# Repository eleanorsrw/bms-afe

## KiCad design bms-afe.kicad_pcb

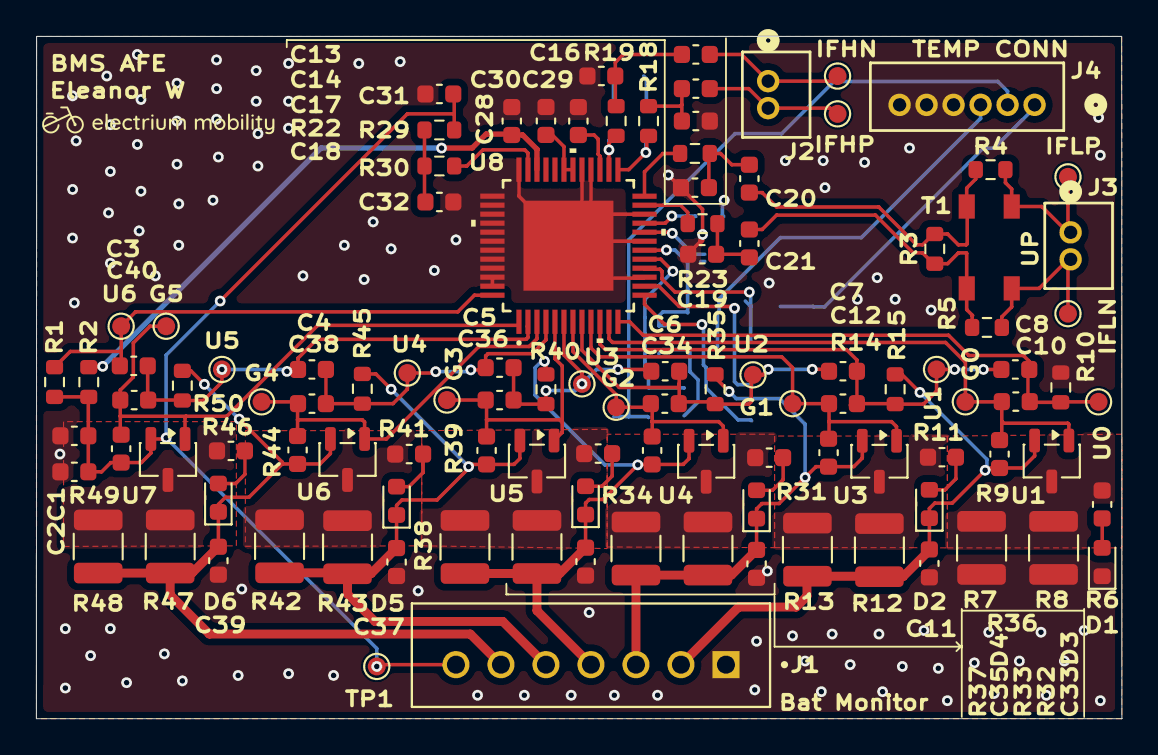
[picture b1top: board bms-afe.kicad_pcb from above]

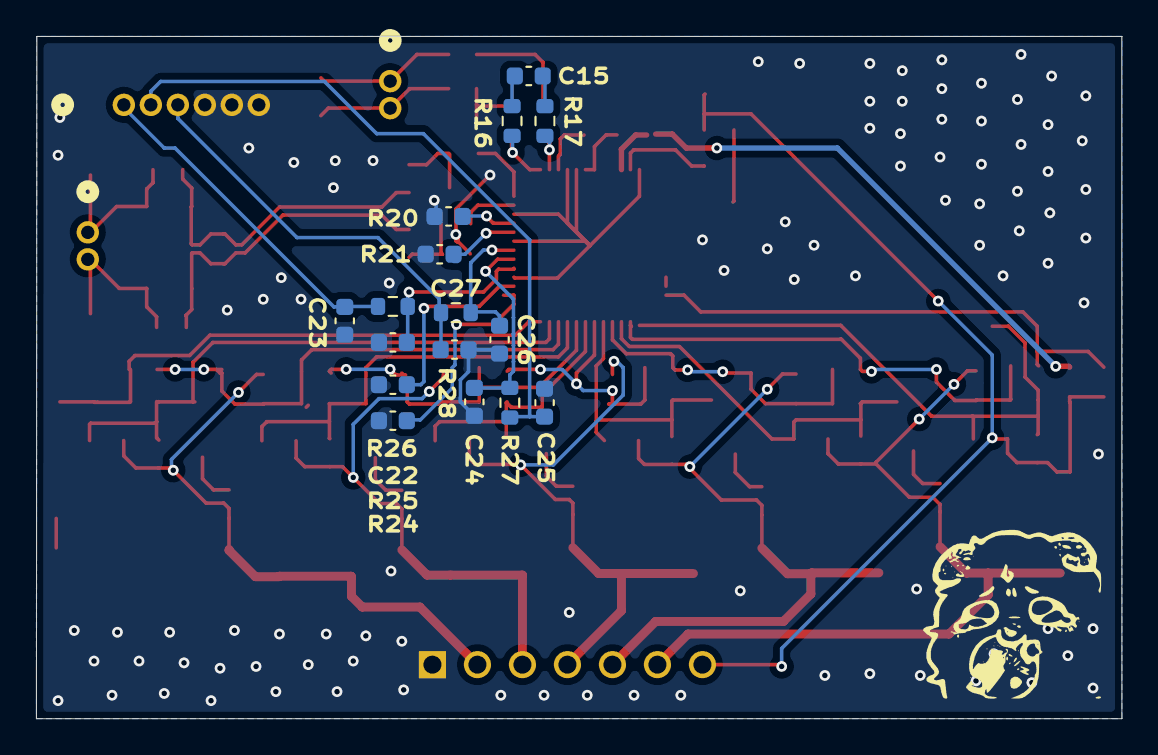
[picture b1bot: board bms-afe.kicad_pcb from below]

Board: 2 copper layers, 60.3 x 37.9 mm, 125 parts (16 on the bottom side), 63 nets.

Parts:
C1, C2, C11, C33, C35, C37, C39: CAP CER 1000PF 50V X7R 0603; C_0603_1608Metric
C3, C4, C5, C6, C7, C8: CAP CER 0.33UF 16V X7R 0603; C_0603_1608Metric
C10, C12, C34, C36, C38, C40: CAP CER 0.1UF 25V X7R 0603; C_0603_1608Metric
C13, C14, C20, C21: CAP CER 0603 1NF 16V X7R 10%; C_0603_1608Metric
C15: CAP CER 250PF 25V NP0 0603; C_0603_1608Metric
C16, C17, C18, C19: CAP CER 220PF 50V X7R 0603; C_0603_1608Metric
C22, C24, C26: 10nF; C_0603_1608Metric
C23, C25, C27: 4.7nF; C_0603_1608Metric
C28: 0.1uF; C_0603_1608Metric
C29: 0.33uF; C_0603_1608Metric
C30, C32: 100nF; C_0603_1608Metric
C31: 1nF; C_0603_1608Metric
D1, D2, D3, D4, D5, D6: 1.6X0.8MM RED/WHT SMD LED; D_0603_1608Metric
G0, G1, G2, G3, G4, G5: TestPoint; TestPoint_Pad_D1.0mm
IFHN: TestPoint; TestPoint_Pad_D1.0mm
IFHP: TestPoint; TestPoint_Pad_D1.0mm
IFLN: TestPoint; TestPoint_Pad_D1.0mm
IFLP: TestPoint; TestPoint_Pad_D1.0mm
J1: CONN HEADER VERT 7POS 2.5MM; JST_B7B-XH-A_LF__SN_
J2, J3: CONN HEADER VERT 2POS 1.5MM; CONN_B2B-ZR_02P_JST
J4: CONN HEADER VERT 6POS 1.5MM; CONN_B6B-ZR_JST
R1, R10, R15, R35, R40, R45, R50: RES 10 OHM 1% 1/10W 0603; R_0603_1608Metric
R2: RES SMD 5.1 OHM 1% 1/8W 0603; R_0603_1608Metric
R3: RES SMD 1K OHM 0.1% 1/10W 0603; R_0603_1608Metric
R4, R5: 0; R_0603_1608Metric
R6, R11, R31, R36, R41, R46: RES SMD 487 OHM 1% 1/10W 0603; C_0603_1608Metric
R7, R8, R12, R13, R32, R33, R37, R38, R42, R43, R47, R48: RES SMD 52.3 OHM 1% 1/2W 1210; C_1210_3225Metric
R9, R14, R34, R39, R44, R49: RES SMD 8.2 OHM 1% 1/8W 0603; C_0603_1608Metric
R16, R26: RES 100 OHM 1% 1/10W 0603; R_0603_1608Metric
R17: 100; R_0603_1608Metric
R18, R19, R22, R23: RES SMD 39 OHM 5% 1/8W 0603; R_0603_1608Metric
R20, R21, R24, R25: 20k; C_0603_1608Metric
R27, R28: RES SMD 10K OHM 1% 1/8W 0603; R_0603_1608Metric
R29: 10; R_0603_1608Metric
R30: 5.1; R_0603_1608Metric
T1: PULSE XFMR 15UH 1 OHM FOR PLC; AMT45S-150-2P-TL000
TP1: TestPoint; TestPoint_Pad_D1.0mm
U0, U1, U2, U3#2, U4#2, U5#2, U6#2: TestPoint; TestPoint_Pad_D1.0mm
U1#2, U3, U4, U5, U6, U7: MOSFET, P-CH, SINGLE, -4.1A, -30; SOT-23-3
U8: TLE9012DQUXUMA1; PG-TQFP-48-9

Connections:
/AFEIC/G0: C10.1, G0.1 (1_1), R9.1, U1#2.1 (G), U8.11 (G0)
/AFEIC/G1: C12.1, G1.1 (1_1), R14.1, U3.1 (G), U8.9 (G1)
/AFEIC/G2: C34.1, G2.1 (1_1), R34.1, U4.1 (G), U8.7 (G2)
/AFEIC/G3: C36.1, G3.1 (1_1), R39.1, U5.1 (G), U8.5 (G3)
/AFEIC/G4: C38.1, G4.1 (1_1), R44.1, U6.1 (G), U8.3 (G4)
/AFEIC/G5: C40.1, G5.1 (1_1), R49.1, U7.1 (G), U8.1 (G5)
/AFEIC/IFH_Filt_N: R17.2, R18.2, U8.26 (IFH_L)
/AFEIC/IFH_Filt_P: R16.2, R19.2, U8.25 (IFH_H)
/AFEIC/IFH_N: C13.1, IFHN.1 (1_1), J2.1
/AFEIC/IFH_P: C14.1, IFHP.1 (1_1), J2.2
/AFEIC/IFL_Filt_N: R23.1, U8.23 (IFL_L)
/AFEIC/IFL_Filt_P: R22.1, U8.24 (IFL_H)
/AFEIC/IFL_N: C21.2, R3.1, R5.1, T1.4
/AFEIC/IFL_P: C20.2, R3.2, R4.1, T1.1
/AFEIC/TMP0: C27.1, J4.3, R28.2
/AFEIC/TMP1: C25.1, J4.2, R27.2
/AFEIC/TMP2: C23.1, J4.1, R26.2
/AFEIC/U0: C8.2, C10.2, R10.2, U0.1 (1_1), U8.12 (U0)
/AFEIC/U1: C7.2, C8.1, C12.2, R15.2, U1.1 (1_1), U8.10 (U1)
/AFEIC/U2: C6.2, C7.1, C34.2, R35.2, U2.1 (1_1), U8.8 (U2)
/AFEIC/U3: C5.2, C6.1, C36.2, R40.2, U3#2.1 (1_1), U8.6 (U3)
/AFEIC/U4: C4.2, C5.1, C38.2, R45.2, U4#2.1 (1_1), U8.4 (U4)
/AFEIC/U5: C3.2, C4.1, C40.2, R50.2, U5#2.1 (1_1), U8.2 (U5)
/AFEIC/U6: C3.1, R1.2, U6#2.1 (1_1), U8.48 (U6)
/AFEIC/U12P: C1.2, C2.2, C31.1, J1.7, R1.1, R2.1, R29.1, R49.2, TP1.1 (1_1), U7.2 (S)
/AFEIC/VREGOUT: C30.1, U8.30 (VIO), U8.31 (VREGOUT)
/CellBalance1/Battery_Pos: C33.2, D3.1 (K), J1.3, R14.2, R32.2, R33.2, R35.1, U3.2 (S)
/CellBalance2/Battery_Pos: C35.2, D4.1 (K), J1.4, R34.2, R37.2, R38.2, R40.1, U4.2 (S)
/CellBalance3/Battery_Pos: C37.2, D5.1 (K), J1.5, R39.2, R42.2, R43.2, R45.1, U5.2 (S)
/CellBalance4/Battery_Pos: C39.2, D6.1 (K), J1.6, R44.2, R47.2, R48.2, R50.1, U6.2 (S)
/CellBalance/Battery_Pos: C11.2, D2.1 (K), J1.2, R9.2, R12.2, R13.2, R15.1, U1#2.2 (S)
BATGND: C1.1, C2.1, C11.1, C16.2, C17.2, C18.2, C19.2, C22.2, C23.2, C24.2, C25.2, C26.2, C27.2, C28.2, C29.2, C30.2, C31.2, C32.2, C33.1, C35.1, C37.1, C39.1, D1.1 (K), J1.1, J4.4, J4.5, J4.6, R7.2, R8.2, R10.1, R20.2, R21.2, R24.2, R25.2, U8.15 (GND), U8.19 (TMP_GND), U8.22 (GND), U8.28 (GPIO0/UART_LS), U8.29 (GPIO1/UART_HS), U8.36 (U12), U8.37 (G11), U8.38 (U11), U8.39 (G10), U8.40 (U10), U8.41 (G9), U8.42 (U9), U8.43 (G8), U8.44 (U8), U8.45 (G7), U8.46 (U7), U8.47 (G6), U8.49 (EPAD)
unnamed: C13.2, C16.1, R18.1
unnamed: C14.2, C17.1, R19.1
unnamed: C15.1, R17.1
unnamed: C15.2, R16.1
unnamed: C18.1, C20.1, R22.2
unnamed: C19.1, C21.1, R23.2
unnamed: C32.1, R29.2, R30.1
unnamed: D1.2 (A), R6.1
unnamed: D2.2 (A), R11.1
unnamed: D3.2 (A), R31.1
unnamed: D4.2 (A), R36.1
unnamed: D5.2 (A), R41.1
unnamed: D6.2 (A), R46.1
unnamed: IFLP.1 (1_1), J3.1, R4.2, T1.2
unnamed: IFLN.1 (1_1), J3.2, R5.2, T1.3
unnamed: R6.2, R7.1, R8.1, U1#2.3 (D)
unnamed: R11.2, R12.1, R13.1, U3.3 (D)
unnamed: R31.2, R32.1, R33.1, U4.3 (D)
unnamed: R36.2, R37.1, R38.1, U5.3 (D)
unnamed: R41.2, R42.1, R43.1, U6.3 (D)
unnamed: R46.2, R47.1, R48.1, U7.3 (D)
unnamed: R20.1, U8.21 (PWM0)
unnamed: R21.1, U8.20 (PWM1)
unnamed: C26.1, R28.1, U8.18 (TMP0)
unnamed: C24.1, R27.1, U8.17 (TMP1)
unnamed: C22.1, R26.1, U8.16 (TMP2)
unnamed: R25.1, U8.14 (TMP3)
unnamed: R24.1, U8.13 (TMP4)
unnamed: R30.2, U8.35 (U12P)
unnamed: C29.1, U8.27 (VDDC)
VBLK: C28.1, R2.2, U8.34 (VS)

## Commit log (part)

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2026-06-18 Add gitignore for KiCad backups
2026-06-19 Add BMS AFE schematic, PCB, and library
2026-06-21 added hierarchy
2026-06-22 mostly done afe ic
2026-06-22 schematic done except for pulse transformer
2026-06-22 fixed balancing module and added pulse transformer
2026-06-23 finished schematic
2026-06-25 updated library
2026-06-25 Add connector footprint and 3D model
2026-06-26 added leds and updated library
2026-06-28 Add new BMS footprints and 3D models
2026-06-28 added led resistor
2026-06-29 fixed minor changes
2026-06-29 passive values
2026-06-30 cleaned up schematic
2026-06-30 added damping resistor on other side of pulse transformer
2026-06-30 fixed capacitor values
2026-06-30 minor changes
